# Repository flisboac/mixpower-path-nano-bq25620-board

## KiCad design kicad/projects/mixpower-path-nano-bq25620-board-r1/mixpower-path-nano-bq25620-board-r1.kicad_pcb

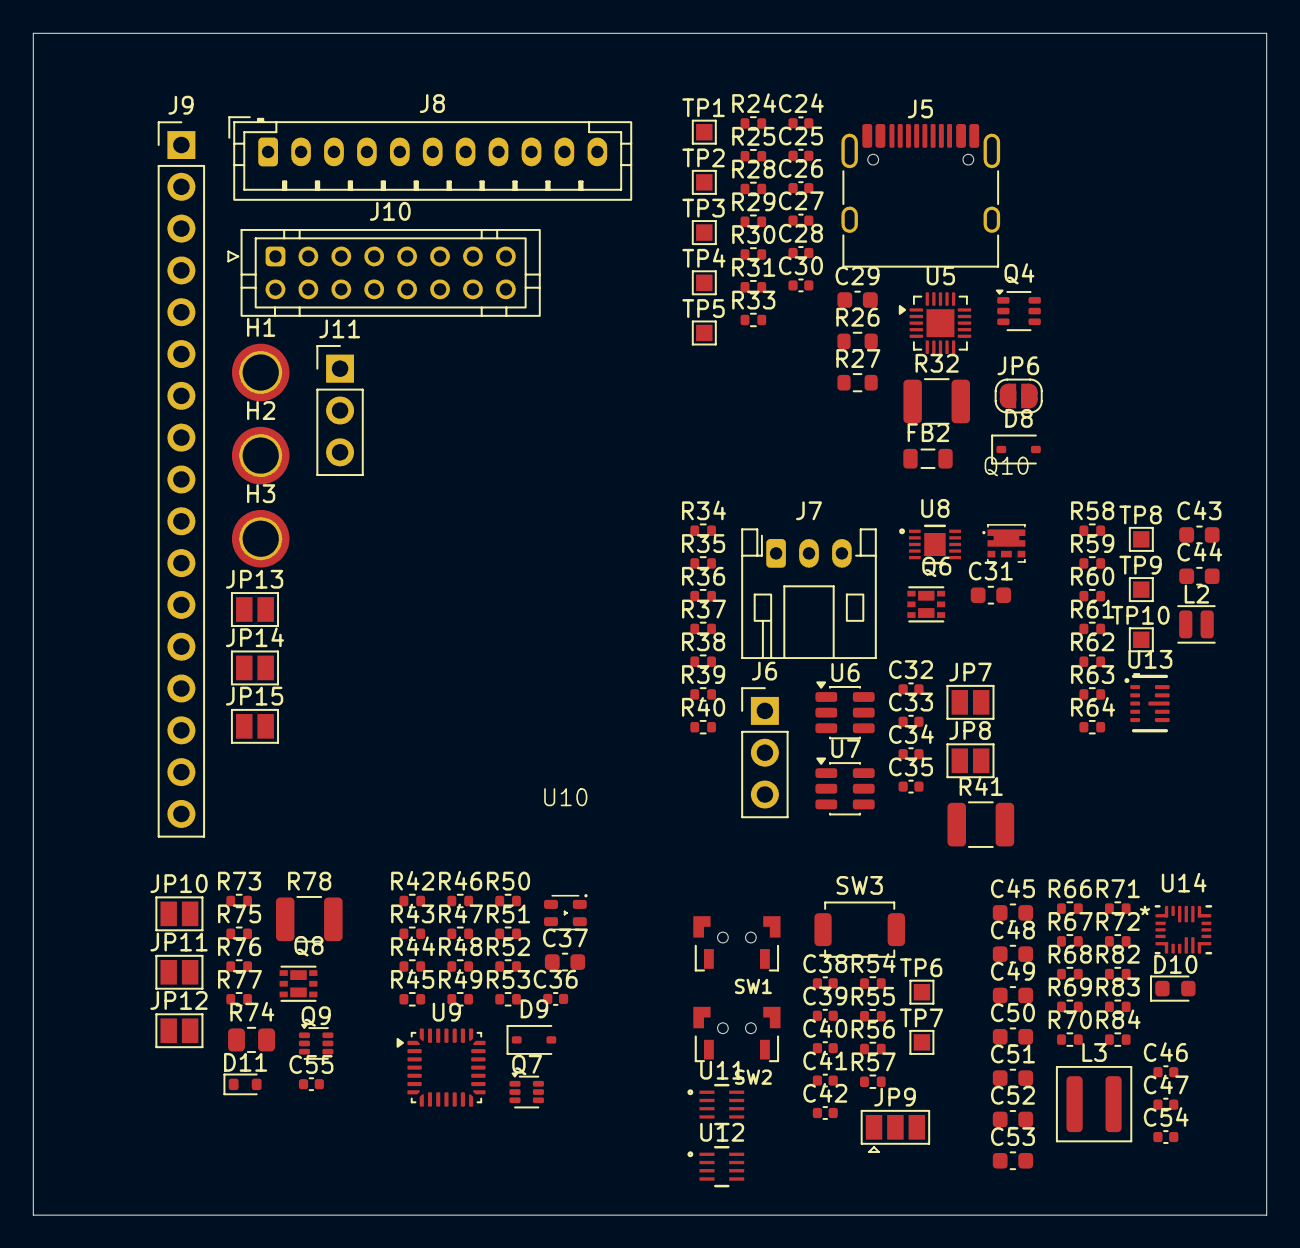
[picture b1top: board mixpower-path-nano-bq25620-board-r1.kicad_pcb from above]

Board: 4 copper layers, 74.9 x 71.8 mm, 145 parts (0 on the bottom side), 93 nets.

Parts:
C24, C35: 1u; C_0402_1005Metric
C25, C27: 2.2u; C_0402_1005Metric
C26, C32, C33, C34, C36, C38, C39, C40, C41, C47, C54, C55: 100n; C_0402_1005Metric
C28, C30: 330n; C_0402_1005Metric
C29, C37, C43, C45, C50, C51, C52, C53: 10u; C_0603_1608Metric
C31: 2.2u; C_0603_1608Metric
C42: 10u; C_0402_1005Metric
C44, C48, C49: 22u; C_0603_1608Metric
C46: 47n; C_0402_1005Metric
D8: PESD24VV1BA; D_SOD-323
D9: 1N5817WS; D_SOD-323
D10: RED; LED_0603_1608Metric
D11: BZX584C18; D_SOD-523
FB2: BLM21PG300SN1D; L_0805_2012Metric
H1, H2, H3: M1; MountingHole_2.2mm_M2_ISO7380_Pad_TopBottom
J5: USB_C_Receptacle_USB2.0_16P; USB_C_Receptacle_HRO_TYPE-C-31-M-12
J6: BAT_HEADERS; PinHeader_1x03_P2.54mm_Vertical
J7: BATT; JST_PH_S3B-PH-K_1x03_P2.00mm_Horizontal
J8: DATA_CONN; JST_PH_B11B-PH-K_1x11_P2.00mm_Vertical
J9: DATA_HEADER; PinHeader_1x17_P2.54mm_Vertical
J10: HAT; JST_PHD_B16B-PHDSS_2x08_P2.00mm_Vertical
J11: DEBUG; PinHeader_1x03_P2.54mm_Vertical
JP6: USB_GND_TO_SHIELD; SolderJumper-2_P1.3mm_Open_RoundedPad1.0x1.5mm
JP7: THRM_BYPASS; SolderJumper-2_P1.3mm_Open_Pad1.0x1.5mm
JP8: BATPROT_BYPASS; SolderJumper-2_P1.3mm_Open_Pad1.0x1.5mm
JP9: EXT_BOOT_SEL; SolderJumper-3_P1.3mm_Open_Pad1.0x1.5mm
JP10: VDD1_VOTG; SolderJumper-2_P1.3mm_Open_Pad1.0x1.5mm
JP11: VDD1_VSYS; SolderJumper-2_P1.3mm_Open_Pad1.0x1.5mm
JP12: VDD1_3V3; SolderJumper-2_P1.3mm_Open_Pad1.0x1.5mm
JP13: H1_SHIELD_TO_GND; SolderJumper-2_P1.3mm_Open_Pad1.0x1.5mm
JP14: H2_SHIELD_TO_GND; SolderJumper-2_P1.3mm_Open_Pad1.0x1.5mm
JP15: H3_SHIELD_TO_GND; SolderJumper-2_P1.3mm_Open_Pad1.0x1.5mm
L2: 470n; L_Changjiang_FTC201612S
L3: 1u; L_Coilcraft_XAL4040-XXX
Q4: Si1539CDL; SOT-363_SC-70-6
Q6: DMN3032LFDBQ; Diodes-Incorporated_U-DFN2020-6_Type-B
Q7, Q9: Si1026X; SOT-563
Q8: SIA931DJ; Diodes-Incorporated_U-DFN2020-6_Type-B
Q10: NTLJS17D0P03P8Z; vendor-onsemi-483av
R24, R25, R69: 5.1k; R_0402_1005Metric
R26, R27: 27; R_0603_1608Metric
R28, R31, R34: 2; R_0402_1005Metric
R29, R30, R33, R42, R46, R58, R59, R60, R64, R66, R67, R71, R73, R75, R77: 1M; R_0402_1005Metric
R32, R78: 1k; R_1210_3225Metric
R35, R39, R54, R55, R57: 10k; R_0402_1005Metric
R36: 100; R_0402_1005Metric
R37, R40, R53, R61, R72, R82, R83, R84: 0; R_0402_1005Metric
R38, R48, R49, R50, R56: 1k; R_0402_1005Metric
R41: 0.01; R_1210_3225Metric
R43, R44, R45, R47, R51, R52: 4.7k; R_0402_1005Metric
R62: 511k; R_0402_1005Metric
R63: 91k; R_0402_1005Metric
R68: 2.2k; R_0402_1005Metric
R70: 30k; R_0402_1005Metric
R74: 220; R_0805_2012Metric
R76: 220; R_0402_1005Metric
SW1, SW2: TS-A002
SW3: TS-1088; SW_SPST_TS-1088-xR020
TP1: D-; TestPoint_Pad_1.0x1.0mm
TP2: D+; TestPoint_Pad_1.0x1.0mm
TP3: CC1; TestPoint_Pad_1.0x1.0mm
TP4: CC2; TestPoint_Pad_1.0x1.0mm
TP5: ~{USBC_FLT}; TestPoint_Pad_1.0x1.0mm
TP6, TP7: SOC_RST_PP; TestPoint_Pad_1.0x1.0mm
TP8: 3V3_EN; TestPoint_Pad_1.0x1.0mm
TP9: 3V3_MODE; TestPoint_Pad_1.0x1.0mm
TP10: 3V3_PG; TestPoint_Pad_1.0x1.0mm
U5: TPD8S300A; vendor-ti-RUK0020B
U6: TS5A3157; SOT-23-6
U7: FS312F-G; SOT-23-6
U8: MAX17055ETB; SPECIFIC_MAX17055ETB_21-100013A_T102A2&plus_1C_MXM
U9: STM32G071G8U6N; QFN-28_4x4mm_P0.5mm
U10: TJ-S1615CY6TGLCCYRGY-A5; LED-3_RGB-0603_1615Metric
U11, U12: RT9829GQW; Specific_DFN8_RT9829_RIT
U13: TPS63802; vendor-ti-DLA0010A
U14: BQ25620; vendor-ti-RYK0018A

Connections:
/input-vbat/BPROT_CS: R38.1, U7.2 (CS)
/input-vbat/BPROT_OC: Q6.5 (G2), U7.3 (OC)
/input-vbat/BPROT_OD: Q6.2 (G1), U7.1 (OD)
/input-vbat/BPROT_VCC: C33.1, R36.2, U7.5 (VCC)
/input-vbat/FG_AIN: R39.2, R40.1, U8.2 (AIN)
/input-vbat/FG_REG: C35.1, U8.7 (REG)
/input-vbat/FG_THRM: R39.1, U8.9 (THRM)
/input-vbat/FG_THRM_AIN: R40.2, U6.1
/input-vbat/THRM: JP7.2 (B), R72.2, U6.3
/input-vbat/THRM_SEL: R37.2, R71.1, U6.6, U14.3 (~PG)
/input-vbat/VBAT: C32.1, C34.1, C51.1, J9.16, Q10.4 (S), Q10.8 (S), R36.1, U8.10 (BATT), U14.8 (BAT)
/input-vbat/VBAT_GND: C34.2, C35.2, JP8.2 (B), Q6.4 (S2), R38.2, R41.1, U8.6 (CSP), U8.11 (EPAD)
/input-vbat/VBAT_GND_IN: C31.2, C33.2, J6.2, J7.2, JP8.1 (A), Q6.1 (S1), R35.2, U7.6 (GND)
/input-vbat/VBAT_GND_MID: Q6.3 (D2), Q6.6 (D1), Q6.7 (D1), Q6.8 (D2)
/input-vbat/VBAT_IN: J6.1, J7.1, Q10.1 (D), Q10.2 (D), Q10.5 (D), Q10.6 (D), Q10.7 (D), R34.1
/input-vbat/VBAT_IN_G: C32.2, Q10.3 (G), R35.1
/input-vbat/VBAT_IN_P: C31.1, R34.2
/input-vbus/SHIELD: H1.1 (1_1), H2.1 (1_1), H3.1 (1_1), J5.SH (SHIELD), JP6.2 (B), JP13.1 (A), JP14.1 (A), JP15.1 (A)
/input-vbus/USBC_CC1: J5.A5 (CC1), R25.1, U5.4 (C_CC1), U5.7 (RPD_G1)
/input-vbus/USBC_CC2: J5.B5 (CC2), R24.1, U5.5 (C_CC2), U5.6 (RPD_G2)
/input-vbus/USBC_D+: J5.A6 (D+), J5.B6 (D+), R27.1, U5.16 (D4), U5.19 (D2)
/input-vbus/USBC_D-: J5.A7 (D-), J5.B7 (D-), R26.1, U5.17 (D3), U5.20 (D1)
/input-vbus/USBC_SBU1: J5.A8 (SBU1), U5.1 (C_SBU1)
/input-vbus/USBC_SBU2: J5.B8 (SBU2), U5.2 (C_SBU2)
/input-vbus/USBC_TPS_VCC: C24.1, Q4.3 (D2), R29.1, U5.10 (VPWR)
/input-vbus/VBUS_DISCH_EN: Q4.2 (G1), R33.1, U9.2 (PC15)
/input-vbus/VBUS_USBC_IN: D8.2 (A2), FB2.1, J5.A4 (VBUS), J5.A9 (VBUS), J5.B4 (VBUS), J5.B9 (VBUS), R28.1
/input-vbus/VBUS_USBC_IN_POST_P: C27.1, R31.2
/input-vbus/VBUS_USBC_IN_PRE_P: C25.1, R28.2
/input-vbus/VPWR_EN: Q4.5 (G2), R30.1, U9.17 (PC6)
/input-vbus/~FLT: R29.2, TP5.1 (1_1), U5.9 (~FLT), U9.1 (PC14)
/output-headers/3V3: C36.1, C37.1, C38.1, C40.1, C44.1, J8.5, J9.5, J10.16, JP12.1 (A), Q4.4 (S2), R43.1, R44.1, R45.1, R47.1, R51.1, R52.1, R54.1, R55.1, R61.2, R64.2, R71.2, SW3.1, U9.3 (VDD), U10.1 (K), U11.8 (VCC), U12.8 (VCC), U13.6 (VOUT)
/output-headers/D+: J8.8, J9.8, R27.2, R82.1, TP2.1 (1_1)
/output-headers/D-: J8.9, J9.9, R26.2, R83.1, TP1.1 (1_1)
/output-headers/DBG_SWCLK: J10.6, J11.3, R53.1, U9.21 (PA14)
/output-headers/DBG_SWDIO: J10.9, J11.1, U9.20 (PA13)
/output-headers/USER1_GP1_SCL_TX: J8.1, J9.1, J10.15, U9.26 (PB6)
/output-headers/USER1_GP2_SDA_RX: J8.3, J9.3, J10.2, U9.27 (PB7)
/output-headers/USER_BOOT: J8.10, J9.10, J10.7, JP9.2 (C)
/output-headers/VBUS: C29.1, C45.1, FB2.2, J8.11, J9.11, J9.13, J10.1, R31.1, R32.1, U14.18 (VBUS)
/output-headers/VDD1: C55.1, J9.12, Q8.3 (D2), Q8.8 (D2_EP), R78.2
/output-headers/VOTG: C52.1, C53.1, C54.1, J9.15, JP10.1 (A), U14.17 (PMID)
/output-headers/VSYS: C43.1, C48.1, C49.1, J9.14, JP11.1 (A), L3.2, R58.2, R60.2, U13.10 (VIN), U14.9 (SYS)
/output-headers/~BTN: C39.1, J8.6, J9.6, J10.14, R54.2, R84.1, SW1.2, U9.28 (PB8), U11.3 (~SR1)
/output-headers/~RST: C41.1, J8.7, J9.7, J10.3, R55.2, SW2.2, U9.5 (PF2), U11.4 (~RST1), U12.3 (~SR1)
/output-headers/~USER_IRQB: D9.2 (A), J8.4, J9.4, J10.12, R52.2, U9.7 (PA1)
/ppc-bc/BC_BTST: C46.2, U14.1 (BTST)
/ppc-bc/BC_STAT: R68.2, U14.10 (STAT)
/ppc-bc/BC_STAT_PRE: D10.1 (K), R68.1
/ppc-bc/BC_THRM: C47.1, R69.1, R70.2, R72.1, U14.6 (TS)
/ppc-bc/VREGN_LP: C50.1, D10.2 (A), R66.1, R69.2, U14.2 (REGN)
/ppc-bc/VSYS_BC_SW: C46.1, L3.1, U14.16 (SW)
/ppc-bc/~CE: R66.2, R67.2, U9.15 (PB15), U14.14 (~CE)
/soc-control/BOOT: C42.1, JP9.1 (A), R53.2, R56.2, R57.1, SW3.2
/soc-control/LED_G: R49.2, U9.11 (PA5)
/soc-control/LED_R: R50.2, U9.12 (PA6)
/soc-control/LED_Y: R48.2, U9.16 (PA8)
/soc-control/PHER1_SCL: J10.13, R47.2, U8.4 (SDA), U9.18 (PA9/PA11), U14.13 (SCL)
/soc-control/PHER1_SDA: J10.4, R45.2, U8.8 (ALRT), U9.19 (PA10/PA12), U14.12 (SDA)
/soc-control/USBC_CC1: C28.1, Q7.6 (D), TP3.1 (1_1), U5.12 (CC1), U9.22 (PD0), U9.23 (PD1)
/soc-control/USBC_CC2: C30.1, Q7.3 (D), TP4.1 (1_1), U5.11 (CC2), U9.24 (PD2), U9.25 (PD3)
/soc-control/USBC_FRSTX1: Q7.2 (G), R42.2, U9.9 (PA3)
/soc-control/USBC_FRSTX2: Q7.5 (G), R46.2, U9.10 (PA4)
/soc-control/USER_IRQB_TX: D9.1 (K), U9.6 (PA0)
/soc-control/VDD1_DISCH_EN: Q9.5 (G), R77.2, U9.13 (PA7)
/soc-control/VDD1_EN: Q9.2 (G), R73.2, U9.14 (PB0)
/soc-control/~PHER1_IRQ1: J10.8, R51.2, U8.3 (SCL), U9.8 (PA2), U14.11 (~INT)
/util-buttons/SRST_BOOT_RST2: R56.1, U12.1 (RST2)
/util-buttons/SRST_RST_RST2: TP6.1 (1_1), U11.1 (RST2)
/util-buttons/~BOOT: JP9.3 (B), TP7.1 (1_1), U12.4 (~RST1)
/vload-vdd1/VDD1_IN: JP10.2 (B), JP11.2 (B), JP12.2 (B), Q8.6 (D1), Q8.7 (D1_EP)
/vload-vdd1/VDD1_MID: D11.1 (K), Q8.1 (S1), Q8.4 (S2), R75.2
/vreg-3v3/EN: R60.1, TP8.1 (1_1), U13.1 (EN)
/vreg-3v3/MODE: R58.1, R59.2, TP9.1 (1_1), U13.2 (MODE)
/vreg-3v3/VSWN_3V3_L1: L2.1, U13.9 (L1)
/vreg-3v3/VSWN_3V3_L2: L2.2, U13.7 (L2)
/vreg-3v3/VSWREG_FB: R62.1, R63.2, U13.4 (FB)
/vreg-3v3/~3V3_PG: R64.1, TP10.1 (1_1), U13.5 (PG)
GND: C24.2, C25.2, C26.2, C27.2, C28.2, C29.2, C30.2, C36.2, C37.2, C38.2, C39.2, C40.2, C41.2, C42.2, C43.2, C44.2, C45.2, C47.2, C48.2, C49.2, C50.2, C51.2, C52.2, C53.2, C54.2, D8.1 (A1), J5.A1 (GND), J5.A12 (GND), J5.B1 (GND), J5.B12 (GND), J8.2, J9.2, J9.17, J10.5, J10.10, J10.11, J11.2, JP6.1 (A), JP13.2 (B), JP14.2 (B), JP15.2 (B), Q4.1 (S1), Q7.1 (S), Q7.4 (S), Q9.1 (S), Q9.4 (S), R24.2, R25.2, R30.2, R33.2, R37.1, R41.2, R42.1, R46.1, R57.2, R59.1, R63.1, R67.1, R70.1, R73.1, R77.1, SW1.1, SW2.1, U5.8 (GND), U5.13 (GND), U5.18 (GND), U5.21 (GND), U6.2 (GND), U8.5 (CSN), U9.4 (VSS), U11.2 (VSS), U11.5 (DSR), U11.7 (~SR0), U12.2 (VSS), U12.5 (DSR), U12.7 (~SR0), U13.3 (AGND), U13.8 (GND), U14.15 (GND)
unnamed: C55.2, R76.2
unnamed: D11.2 (A), Q8.2 (G1), Q8.5 (G2), R74.2, R75.1, R76.1
unnamed: J6.3, J7.3, JP7.1 (A), U6.4
unnamed: Q4.6 (D1), R32.2
unnamed: Q9.6 (D), R74.1
unnamed: Q9.3 (D), R78.1
unnamed: R61.1, R62.2
unnamed: C26.1, U5.3 (VBIAS)
unnamed: R49.1, U10.3 (G)
unnamed: R50.1, U10.4 (R)
unnamed: R48.1, U10.2 (Y)
unnamed: R82.2, U14.5 (D+)
unnamed: R83.2, U14.4 (D-)
unnamed: R84.2, U14.7 (~QON)

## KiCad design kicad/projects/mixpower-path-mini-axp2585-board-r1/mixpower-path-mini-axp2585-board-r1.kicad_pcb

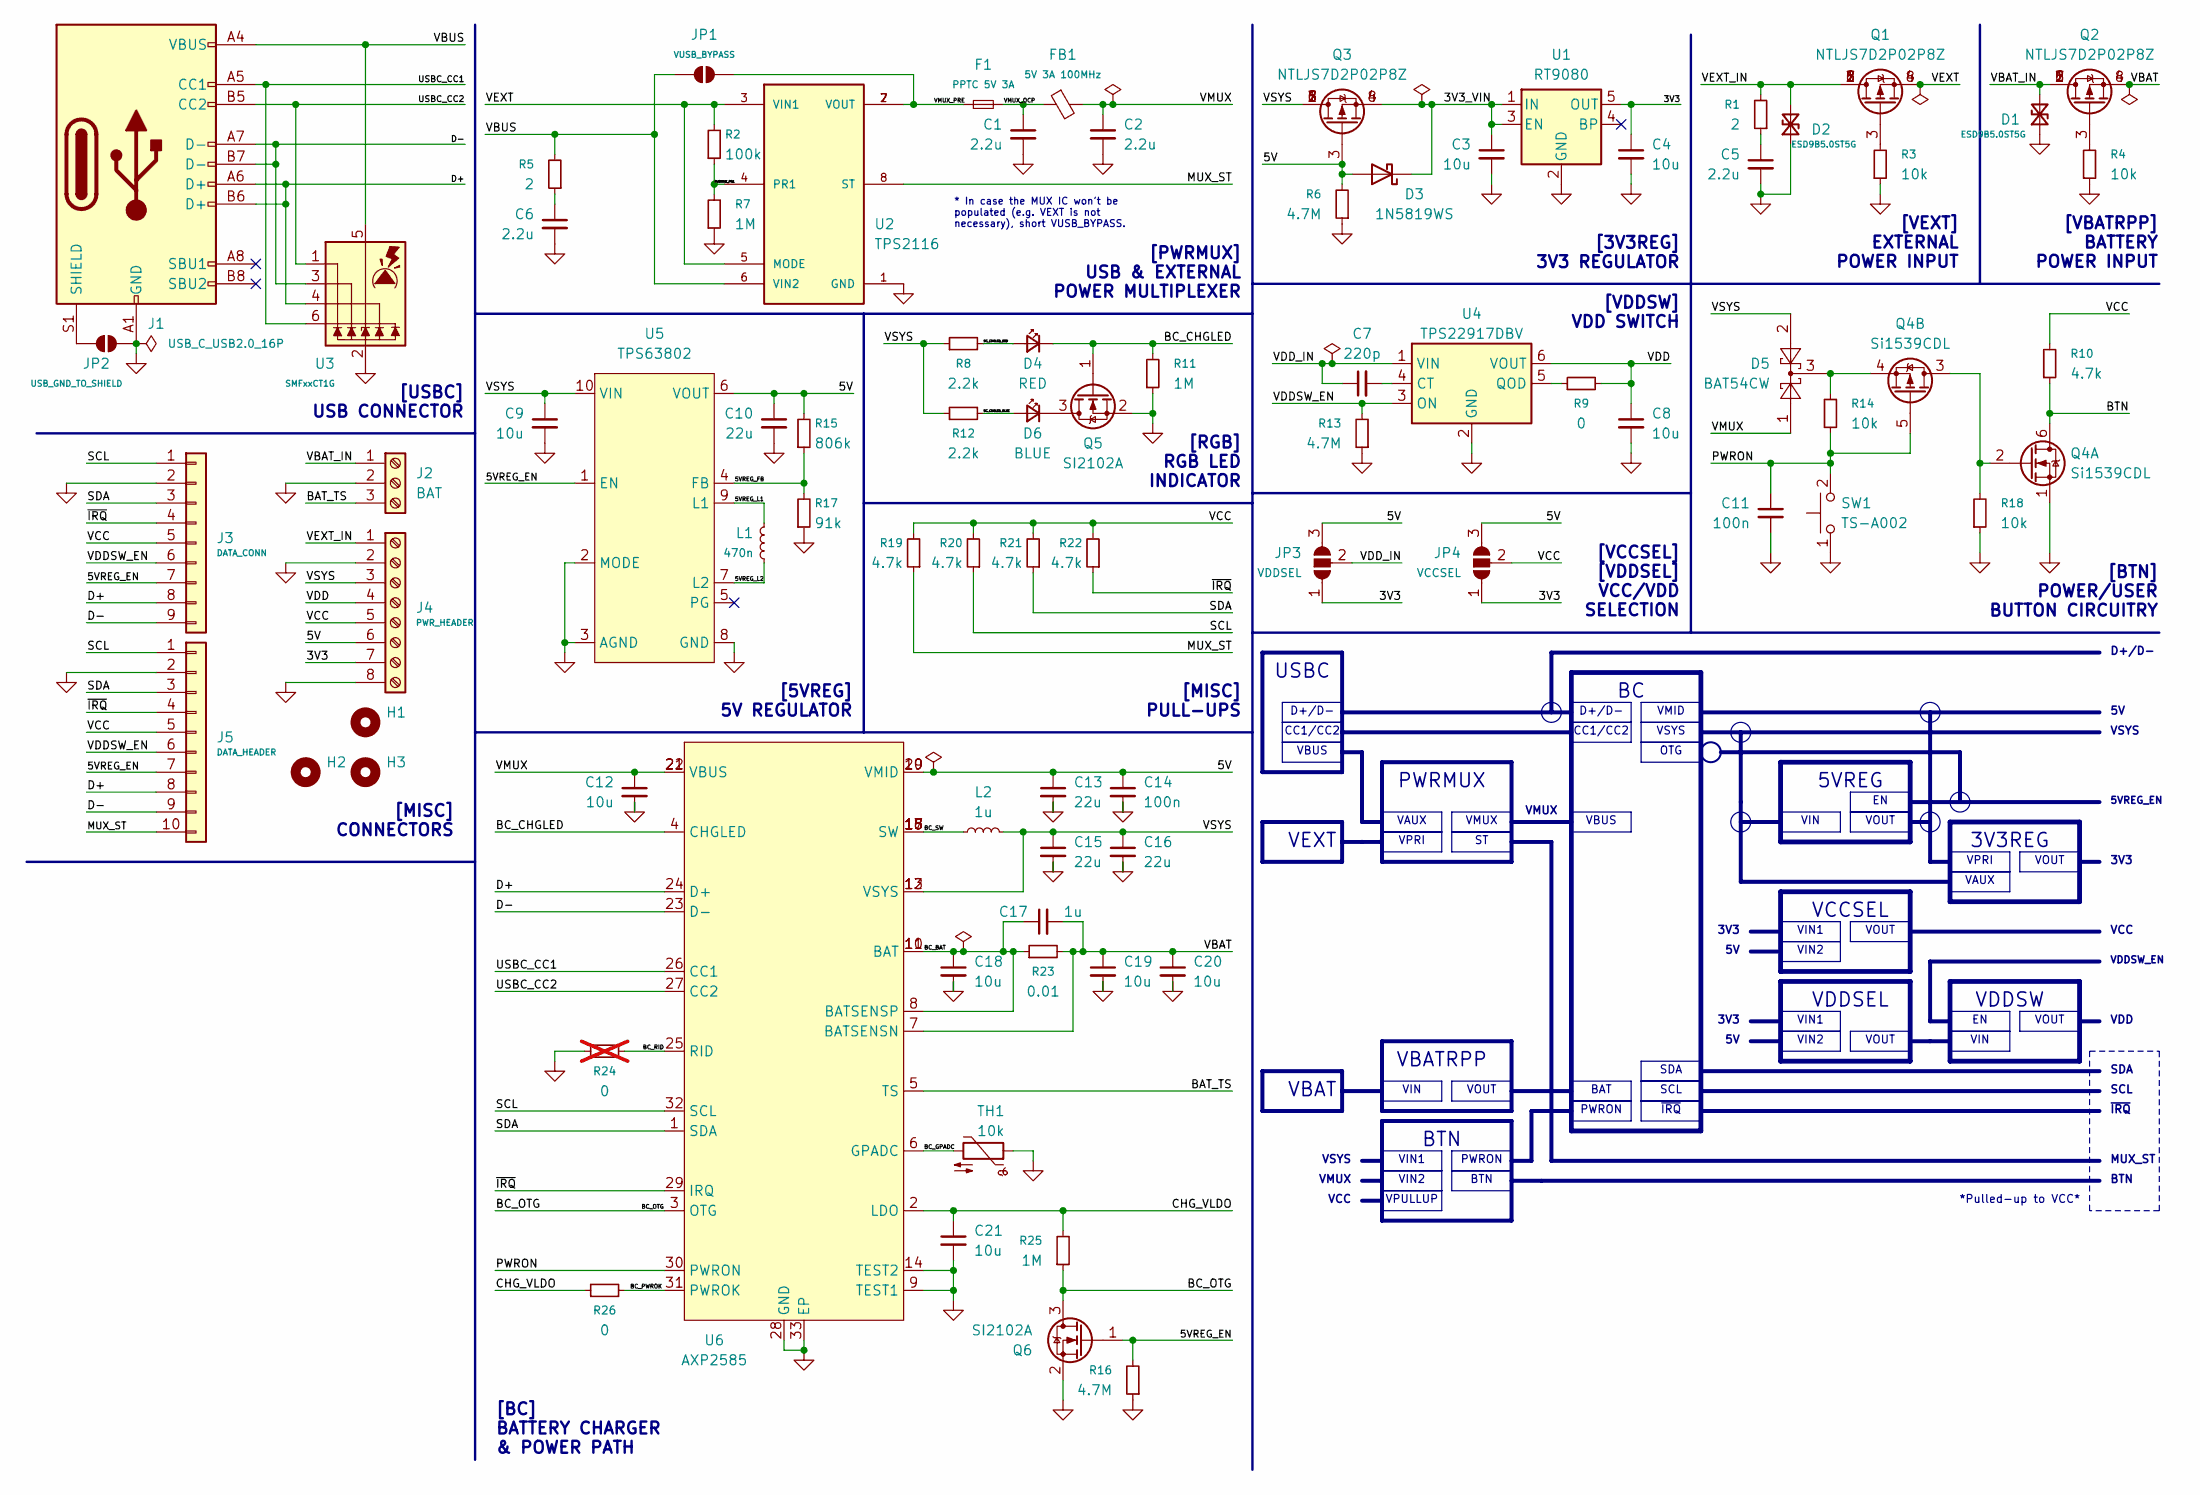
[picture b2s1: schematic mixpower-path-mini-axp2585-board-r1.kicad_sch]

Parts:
C1, C2, C5, C6: 2.2u; C_0402_1005Metric
C3, C4, C8, C12, C18, C19, C20, C21: 10u; C_0402_1005Metric
C7: 220p; C_0402_1005Metric
C9: 10u; C_0603_1608Metric
C10, C13, C15, C16: 22u; C_0603_1608Metric
C11, C14: 100n; C_0402_1005Metric
C17: 1u; C_0402_1005Metric
D1, D2: ESD9B5.0ST5G; D_SOD-923
D3: 1N5819WS; D_SOD-323
D4: RED; LED_0603_1608Metric
D5: BAT54CW; SOT-323_SC-70
D6: BLUE; LED_0603_1608Metric
F1: PPTC 5V 3A; Fuse_1210_3225Metric
FB1: 5V 3A 100MHz; L_1210_3225Metric
H1, H2, H3: MountingHole; MountingHole_2.2mm_M2
J1: USB_C_USB2.0_16P; USB_C_Receptacle_HRO_TYPE-C-31-M-12
J2: BAT; JST_PH_S3B-PH-K_1x03_P2.00mm_Horizontal
J3: DATA_CONN; JST_ZH_B9B-ZR_1x09_P1.50mm_Vertical
J4: PWR_HEADER; PinHeader_1x08_P2.54mm_Vertical
J5: DATA_HEADER; PinHeader_1x10_P2.54mm_Vertical
JP1: VUSB_BYPASS; SolderJumper-2_P1.3mm_Open_RoundedPad1.0x1.5mm
JP2: USB_GND_TO_SHIELD; SolderJumper-2_P1.3mm_Open_RoundedPad1.0x1.5mm
JP3: VDDSEL; SolderJumper-3_P1.3mm_Open_RoundedPad1.0x1.5mm
JP4: VCCSEL; SolderJumper-3_P1.3mm_Open_RoundedPad1.0x1.5mm
L1: 470n; L_Coilcraft_XxL4020
L2: 1u; L_Coilcraft_XAL4020-XXX
Q1, Q2, Q3: NTLJS7D2P02P8Z; vendor-onsemi-483av
Q4: Si1539CDL; SOT-363_SC-70-6
Q5, Q6: SI2102A; SOT-323_SC-70
R1, R5: 2; R_0402_1005Metric
R2: 100k; R_0402_1005Metric
R3, R4, R14, R18: 10k; R_0402_1005Metric
R6, R13, R16: 4.7M; R_0402_1005Metric
R7, R11, R25: 1M; R_0402_1005Metric
R8, R12: 2.2k; R_0402_1005Metric
R9, R26: 0; R_0402_1005Metric
R10, R19, R20, R21, R22: 4.7k; R_0402_1005Metric
R15: 806k; R_0402_1005Metric
R17: 91k; R_0402_1005Metric
R23: 0.01; R_1210_3225Metric
R24: 0; R_0402_1005Metric; not fitted
SW1: TS-A002
TH1: 10k; R_0603_1608Metric
U1: RT9080; SOT-23-5
U2: TPS2116
U3: SMFxxCT1G; SOT-363_SC-70-6
U4: TPS22917DBV; SOT-23-6
U5: TPS63802; vendor-ti-DLA0010A
U6: AXP2585; QFN-32-1EP_5x5mm_P0.4mm_EP3x3mm; LCSC C20199912

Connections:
/3V3: C4.1, J4.7, JP3.1 (A), JP4.1 (A), U1.5 (OUT)
/3V3_VIN: C3.1, D3.1 (K), Q3.4 (S), Q3.8 (S), U1.1 (IN), U1.3 (EN)
/5V: C10.1, C13.1, C14.1, D3.2 (A), J4.6, JP3.3 (B), JP4.3 (B), Q3.3 (G), R6.2, R15.2, U5.6 (VOUT), U6.19 (VMID), U6.20 (VMID)
/5VREG_EN: J2.7, J3.7, J5.7, Q6.1 (G), R16.2, U5.1 (EN)
/5VREG_FB: R15.1, R17.2, U5.4 (FB)
/5VREG_L1: L1.1, U5.9 (L1)
/5VREG_L2: L1.2, U5.7 (L2)
/BC_BAT: C17.1, C18.1, R23.1, U6.8 (BATSENSP), U6.10 (BAT), U6.11 (BAT)
/BC_CHGLED: D4.1 (K), Q5.1 (G), R11.2, U6.4 (CHGLED)
/BC_CHGLED_BLUE: D6.2 (A), R12.2
/BC_CHGLED_RED: D4.2 (A), R8.2
/BC_GPADC: TH1.2, U6.6 (GPADC)
/BC_OTG: Q6.3 (D), R25.1, U6.3 (OTG)
/BC_PWROK: R26.2, U6.31 (PWROK)
/BC_RID: R24.2, U6.25 (RID)
/BC_SW: L2.1, U6.15 (SW), U6.16 (SW), U6.17 (SW), U6.18 (SW)
/BTN: Q4.6 (D1), R10.1
/CHG_VLDO: C21.1, R25.2, R26.1, U6.2 (LDO)
/D+: J1.A6 (D+), J1.B6 (D+), J2.8, J3.8, J5.8, U3.4 (I/O3), U6.24 (D+)
/D-: J1.A7 (D-), J1.B7 (D-), J2.9, J3.9, J5.9, U3.3 (I/O2), U6.23 (D-)
/MUX_ST: J2.10, J5.10, R19.1, U2.8 (ST)
/PWRMUX_PR1: R2.1, R7.2, U2.4 (PR1)
/PWRON: C11.1, Q4.5 (G2), R14.1, SW1.2, U6.30 (PWRON)
/USBC_CC1: J1.A5 (CC1), U3.6 (I/O4), U6.26 (CC1)
/USBC_CC2: J1.B5 (CC2), U3.1 (I/O1), U6.27 (CC2)
/VBAT: C17.2, C19.1, C20.1, Q2.4 (S), Q2.8 (S), R23.2, U6.7 (BATSENSN)
/VBUS: J1.A4 (VBUS), J1.A9 (VBUS), J1.B4 (VBUS), J1.B9 (VBUS), JP1.2 (B), R5.2, U2.6 (VIN2), U3.5 (I/O5)
/VCC: J2.5, J3.5, J4.5, J5.5, JP4.2 (C), R10.2, R19.2, R20.2, R21.2, R22.2
/VDD: C8.1, J4.4, R9.2, U4.6 (VOUT)
/VDDSW_EN: J2.6, J3.6, J5.6, R13.2, U4.3 (ON)
/VDD_IN: C7.1, JP3.2 (C), U4.1 (VIN)
/VEXT: Q1.4 (S), Q1.8 (S), R2.2, U2.3 (VIN1), U2.5 (MODE)
/VEXT_IN: D2.2 (A2), J4.1, Q1.1 (D), Q1.2 (D), Q1.5 (D), Q1.6 (D), Q1.7 (D), R1.2
/VMUX: C2.1, C12.1, D5.1 (A1), FB1.2, U6.21 (VBUS), U6.22 (VBUS)
/VMUX_OCP: C1.1, F1.2, FB1.1
/VMUX_PRE: F1.1, JP1.1 (A), U2.2 (VOUT), U2.7 (VOUT)
/VSYS: C9.1, C15.1, C16.1, D5.2 (A2), J4.3, L2.2, Q3.1 (D), Q3.2 (D), Q3.5 (D), Q3.6 (D), Q3.7 (D), R8.1, R12.1, U5.10 (VIN), U6.12 (VSYS), U6.13 (VSYS)
/~IRQ: J2.4, J3.4, J5.4, R22.1, U6.29 (IRQ)
GND: C1.2, C2.2, C3.2, C4.2, C5.2, C6.2, C8.2, C9.2, C10.2, C11.2, C12.2, C13.2, C14.2, C15.2, C16.2, C18.2, C19.2, C20.2, C21.2, D1.1 (A1), D2.1 (A1), J1.A1 (GND), J1.A12 (GND), J1.B1 (GND), J1.B12 (GND), J2.2, J3.2, J4.2, J4.8, J5.2, JP2.1 (A), Q4.1 (S1), Q5.2 (S), Q6.2 (S), R3.1, R4.1, R6.1, R7.1, R11.1, R13.1, R16.1, R17.1, R18.1, R24.1, SW1.1, TH1.1, U1.2 (GND), U2.1 (GND), U3.2 (GND), U4.2 (GND), U5.2 (MODE), U5.3 (AGND), U5.8 (GND), U6.9 (TEST1), U6.14 (TEST2), U6.28 (GND), U6.33 (EP); also elsewhere on the board
unnamed: C5.1, R1.1
unnamed: C6.1, R5.1
unnamed: D5.3 (K), Q4.4 (S2), R14.2
unnamed: D6.1 (K), Q5.3 (D)
unnamed: J1.S1 (SHIELD), JP2.2 (B)
unnamed: Q1.3 (G), R3.2
unnamed: Q2.3 (G), R4.2
unnamed: Q4.2 (G1), Q4.3 (D2), R18.2
unnamed: C7.2, U4.4 (CT)
unnamed: R9.1, U4.5 (QOD)

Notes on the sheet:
3V3
VIN2
VBUS
~{IRQ}
VEXT
SDA
BTN
*Pulled-up to VCC*
VMUX
[VCCSEL] [VDDSEL] VCC/VDD SELECTION
VIN1
VOUT
VSYS
VBAT
5VREG
VAUX
[BTN] POWER/USER BUTTON CIRCUITRY
PWRMUX
VIN
SCL
CC1/CC2
VDD
PWRON
VCC
D+/D-
VDDSW_EN
* In case the MUX IC won't be populated (e.g. VEXT is not necessary), short VUSB_BYPASS.
VPRI
[VEXT] EXTERNAL POWER INPUT
[PWRMUX] USB & EXTERNAL POWER MULTIPLEXER
[USBC] USB CONNECTOR
3V3REG
VDDSW
~{IRQ}
5VREG_EN
[5VREG] 5V REGULATOR
VDDSEL
VBATRPP
USBC
MUX_ST

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
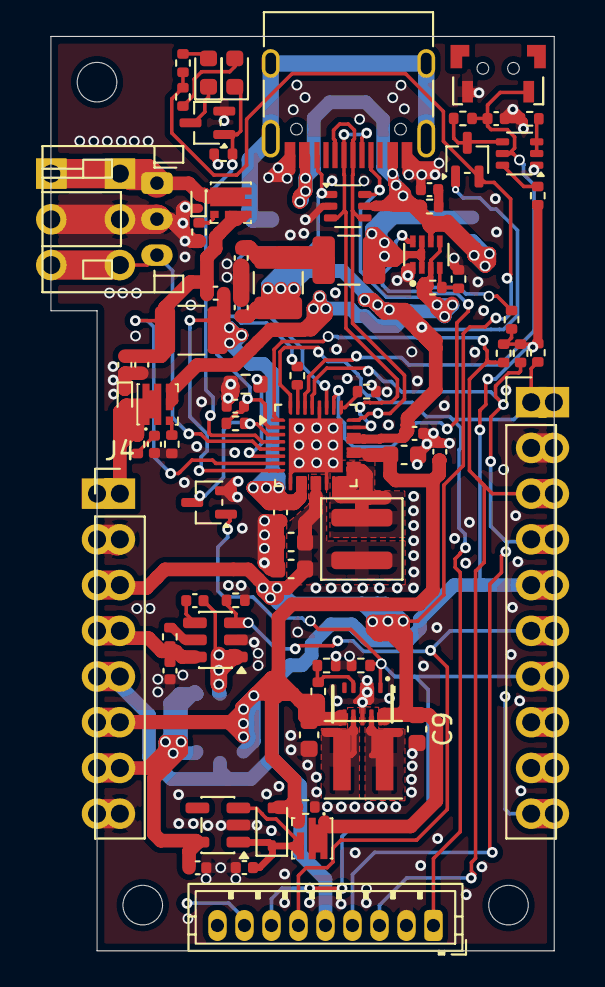
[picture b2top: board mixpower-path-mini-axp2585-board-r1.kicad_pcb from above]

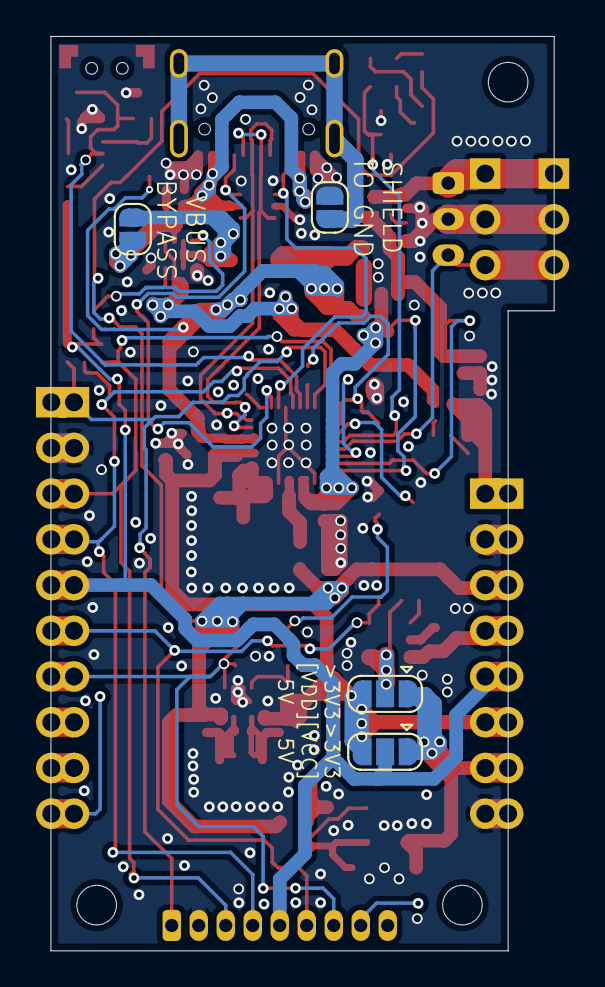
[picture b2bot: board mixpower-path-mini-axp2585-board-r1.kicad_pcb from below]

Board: 4 copper layers, 28.0 x 50.8 mm, 84 parts (4 on the bottom side), 53 nets.

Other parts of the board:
J2#2: BAT; JST_PH_S3B-PH-K_1x03_P2.00mm_Horizontal

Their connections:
GND: J2#2.2; also elsewhere on the board

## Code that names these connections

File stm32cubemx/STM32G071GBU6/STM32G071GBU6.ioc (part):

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Mcu.Name=STM32G071G(8-B)UxN
Mcu.Package=UFQFPN28
Mcu.UserName=STM32G071G8UxN
PA0.GPIOParameters=GPIO_Label
PA0.GPIO_Label=IRQB__USART4_TX__SYS_WKUP1
PA0.Signal=SharedStack_PA0
PA0.Stacked=true
PA1.GPIOParameters=GPIO_Label
PA1.GPIO_Label=IRQB__USART4_RX
PA1.Mode=Asynchronous
PA1.Signal=USART4_RX
PA1.Stacked=true
PA11\ [PA9].GPIOParameters=GPIO_Label
PA11\ [PA9].GPIO_Label=PHER__I2C_SCL
PA11\ [PA9].Mode=I2C
PA11\ [PA9].Signal=I2C2_SCL
PA12\ [PA10].GPIOParameters=GPIO_Label
PA12\ [PA10].GPIO_Label=PHER__I2C_SDA
PA12\ [PA10].Mode=I2C
PA12\ [PA10].Signal=I2C2_SDA
PA13.GPIOParameters=GPIO_Label
PA13.GPIO_Label=MCU__SYS_SWDIO
PA13.Mode=Serial_Wire
PA13.Signal=SYS_SWDIO
PA14-BOOT0.GPIOParameters=GPIO_Label
PA14-BOOT0.GPIO_Label=MCU__SYS_SWCLK__BOOT0
PA14-BOOT0.Mode=Serial_Wire
PA14-BOOT0.Signal=SYS_SWCLK
PA2.GPIOParameters=GPIO_Label
PA2.GPIO_Label=PHER__IRQ1__SYS_WKUP4
PA2.Signal=SharedStack_PA2
PA2.Stacked=true
PA3.Mode=FRSTX_CC2
PA3.Signal=UCPD2_FRSTX1
PA4.Mode=FRSTX_CC2
PA4.Signal=UCPD2_FRSTX2
PA5.GPIOParameters=GPIO_Label
PA5.GPIO_Label=UTIL__LED_G
PA5.Signal=S_TIM2_CH1_ETR
PA6.GPIOParameters=GPIO_Label
PA6.GPIO_Label=UTIL__LED_R
PA6.Signal=S_TIM3_CH1
PA7.GPIOParameters=GPIO_Label
PA7.GPIO_Label=PMIC__VDD1_DISCH_EN
PA7.Signal=GPIO_Output
PA8.GPIOParameters=GPIO_Label
PA8.GPIO_Label=UTIL__LED_Y
PA8.Signal=S_TIM1_CH1
PB0.GPIOParameters=GPIO_Label
PB0.GPIO_Label=PMIC__VDD1_EN
PB0.Signal=GPIO_Output
PB15.GPIOParameters=GPIO_Label
PB15.GPIO_Label=PMIC__BC_CHG_EN
PB15.Signal=GPIO_Input
PB6.GPIOParameters=GPIO_Label
PB6.GPIO_Label=USER__I2C1_SCL__USART1_TX
PB6.Signal=SharedStack_PB6
PB6.Stacked=true
PB7.GPIOParameters=GPIO_Label
PB7.GPIO_Label=USER__I2C1_SDA__USART1_RX
PB7.Signal=SharedStack_PB7
PB7.Stacked=true
PB8.GPIOParameters=GPIO_Label
PB8.GPIO_Label=USER__BTN
PB8.Signal=GPIO_Output
PC14-OSC32_IN\ (PC14).GPIOParameters=GPIO_Label
PC14-OSC32_IN\ (PC14).GPIO_Label=USBC__FAULT
PC14-OSC32_IN\ (PC14).Signal=GPIO_Input
PC15-OSC32_OUT\ (PC15).GPIOParameters=GPIO_Label
PC15-OSC32_OUT\ (PC15).GPIO_Label=USBC__VBUS_DISCH
PC15-OSC32_OUT\ (PC15).Signal=GPIO_Output
PC6.GPIOParameters=GPIO_Label
PC6.GPIO_Label=USBC__VPWR_EN
PC6.Signal=GPIO_Output
PD0.GPIOParameters=GPIO_Label
PD0.GPIO_Label=USBC__UCPD2_CC1
PD0.Mode=Dual_Role_AllSignals
PD0.Signal=UCPD2_CC1
PD1.GPIOParameters=GPIO_Label
PD1.GPIO_Label=USBC__UCPD2__DBCC1
PD1.Mode=EnableDeadBattery
PD1.Signal=UCPD2_DBCC1
PD2.GPIOParameters=GPIO_Label
PD2.GPIO_Label=USBC__UCPD2_CC2
PD2.Mode=Dual_Role_AllSignals
PD2.Signal=UCPD2_CC2
PD3.GPIOParameters=GPIO_Label
PD3.GPIO_Label=USBC__UCPD2_DBCC2
PD3.Mode=EnableDeadBattery
PD3.Signal=UCPD2_DBCC2
PF2\ -\ NRST.GPIOParameters=GPIO_Label
PF2\ -\ NRST.GPIO_Label=MCU__RESET
PF2\ -\ NRST.Signal=GPIO_Input
RCC.HSE_VALUE=8000000
RCC.SYSCLKFreq_VALUE=16000000
board=custom

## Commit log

2026-02-16 feat: initial commit just to do a copier update
2026-02-23 refactor: small adjustments
2026-02-23 fix: non-electrical/ small fixes to the schematic
2026-03-30 feat: implement the schematics and base project ideas/layout
2026-03-30 feat: add pinouts created in STM32CubeMX for the STM32G071G8U6N
2026-04-05 feat: rework schematics and add proper calculations
2026-04-05 chore: regenerate schematics plots
2026-04-05 fix: add project metadata and plot schematics
2026-04-05 fix: put all subsheets in root of the Kicad project, regenerate schematics plots
